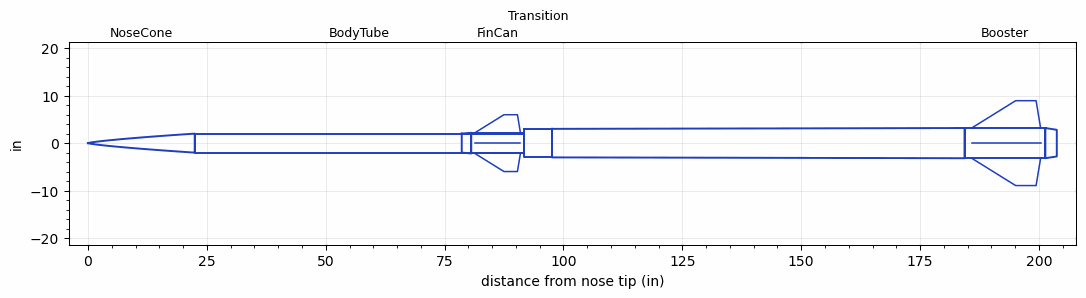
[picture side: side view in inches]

<RASAeroDocument>
 <FileVersion>2</FileVersion>
 <RocketDesign>
  <NoseCone>
   <Length>22.44</Length>
   <Diameter>4</Diameter>
   <Shape>Power Law</Shape>
   <BluntRadius>0.0825</BluntRadius>
   <Location>0</Location>
   <PowerLaw>0.75</PowerLaw>
  </NoseCone>
  <BodyTube>
   <Length>69.16</Length>
   <Diameter>4</Diameter>
   <Location>22.44</Location>
  </BodyTube>
  <FinCan>
   <Length>11</Length>
   <Diameter>4.35</Diameter>
   <InsideDiameter>4</InsideDiameter>
   <Location>91.60001</Location>
   <ShoulderLength>2</ShoulderLength>
   <Offset>-11</Offset>
   <Fin>
    <Count>4</Count>
    <Chord>9.57</Chord>
    <Span>3.8</Span>
    <SweepDistance>6.105</SweepDistance>
    <TipChord>2.84</TipChord>
    <Thickness>0.25</Thickness>
    <LERadius>0.08</LERadius>
    <Location>10.23</Location>
    <AirfoilSection>Hexagonal</AirfoilSection>
    <FX1>0.5</FX1>
    <FX3>0.5</FX3>
   </Fin>
  </FinCan>
  <Transition>
   <Length>6</Length>
   <Diameter>6</Diameter>
   <Location>91.60001</Location>
   <RearDiameter>6</RearDiameter>
  </Transition>
  <Booster>
   <Length>17</Length>
   <Diameter>6.35</Diameter>
   <InsideDiameter>6</InsideDiameter>
   <Location>97.60001</Location>
   <ShoulderLength>86.75</ShoulderLength>
   <BoattailLength>2.4</BoattailLength>
   <BoattailRearDiameter>5.6</BoattailRearDiameter>
   <Fin>
    <Count>4</Count>
    <Chord>14.5</Chord>
    <Span>5.75</Span>
    <SweepDistance>9.25</SweepDistance>
    <TipChord>4.3</TipChord>
    <Thickness>0.25</Thickness>
    <LERadius>0.08</LERadius>
    <Location>15.5</Location>
    <AirfoilSection>Hexagonal</AirfoilSection>
    <FX1>0.5</FX1>
    <FX3>0.5</FX3>
   </Fin>
  </Booster>
  <Surface>Cast Iron (Very Rough)</Surface>
  <ModifiedBarrowman>False</ModifiedBarrowman>
  <Turbulence>False</Turbulence>
  <UseBooster1>False</UseBooster1>
  <UseBooster2>False</UseBooster2>
 </RocketDesign>
 <LaunchSite>
  <Altitude>3000</Altitude>
  <Pressure>0</Pressure>
  <RodAngle>0</RodAngle>
  <RodLength>18</RodLength>
  <Temperature>85</Temperature>
  <WindSpeed>8</WindSpeed>
 </LaunchSite>
 <Recovery>
  <Altitude1>1000</Altitude1>
  <Altitude2>1000</Altitude2>
  <DeviceType1>None</DeviceType1>
  <DeviceType2>None</DeviceType2>
  <Event1>False</Event1>
  <Event2>False</Event2>
  <Size1>1</Size1>
  <Size2>1</Size2>
  <EventType1>None</EventType1>
  <EventType2>None</EventType2>
  <CD1>1.33</CD1>
  <CD2>1.33</CD2>
 </Recovery>
 <SimulationList>
  <Simulation>
   <SustainerEngine>O4200  (O4200)</SustainerEngine>
   <SustainerLaunchWt>60</SustainerLaunchWt>
   <SustainerCG>60</SustainerCG>
   <SustainerIgnitionDelay>0</SustainerIgnitionDelay>
   <Booster1Engine>P9095  (MIT)</Booster1Engine>
   <Booster1LaunchWt>170</Booster1LaunchWt>
   <Booster1SeparationDelay>0</Booster1SeparationDelay>
   <Booster1IgnitionDelay>0</Booster1IgnitionDelay>
   <Booster1CG>120</Booster1CG>
   <IncludeBooster1>True</IncludeBooster1>
   <Booster2Delay>0</Booster2Delay>
   <IncludeBooster2>False</IncludeBooster2>
   <TimetoApogee>126.0569</TimetoApogee>
   <MaxAltitude>243806.6</MaxAltitude>
   <MaxVelocity>4699.679</MaxVelocity>
  </Simulation>
 </SimulationList>
</RASAeroDocument>
